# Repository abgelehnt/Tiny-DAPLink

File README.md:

# Tiny-DAPLink

> 小巧的使用CH552实现的DAPLink

详见[Tiny-DAPLink：开源CH552实现的CMSIS-DAP v2升级版](https://whycan.com/t_9365.html)

## 硬件设计

1. 下载按键需要超级小的两脚小龟按键，如果不重复下载调试，可以不焊
2. 整体需要包热缩管进行绝缘，不然手汗会造成数据异常

## DAT命令列表

使用任意串口工具发送特定的命令即可对Tiny-DAPLink进行相应的设置。

| 命令            | 描述                                                 |
|:--------------|:---------------------------------------------------|
| DAT+RST       | 重启调试器                                              |
| DAT+IAP       | 进入调试器固件下载模式                                        |
| DAT+KEY?      | 查询电容键盘映射的按键                                        |
| DAT+KEY=XX    | 更改电容键盘映射的按键[USB CDC键盘键值表](3.Docs/Keyboard_HID.txt) |
| DAT+KEY=FF    | 关闭电容键盘功能                                           |
| DAT+AUTHOR?   | 查询作者信息                                             |
| DAT+KEY_FLASH | 刷新电容按键参数                                           |
| DAT+KEY_VALUE | 查看电容按键参数                                           |

## 注意事项

1. 一些不合格的数据线会使Type C接口外壳对地短路，使电容按键失效

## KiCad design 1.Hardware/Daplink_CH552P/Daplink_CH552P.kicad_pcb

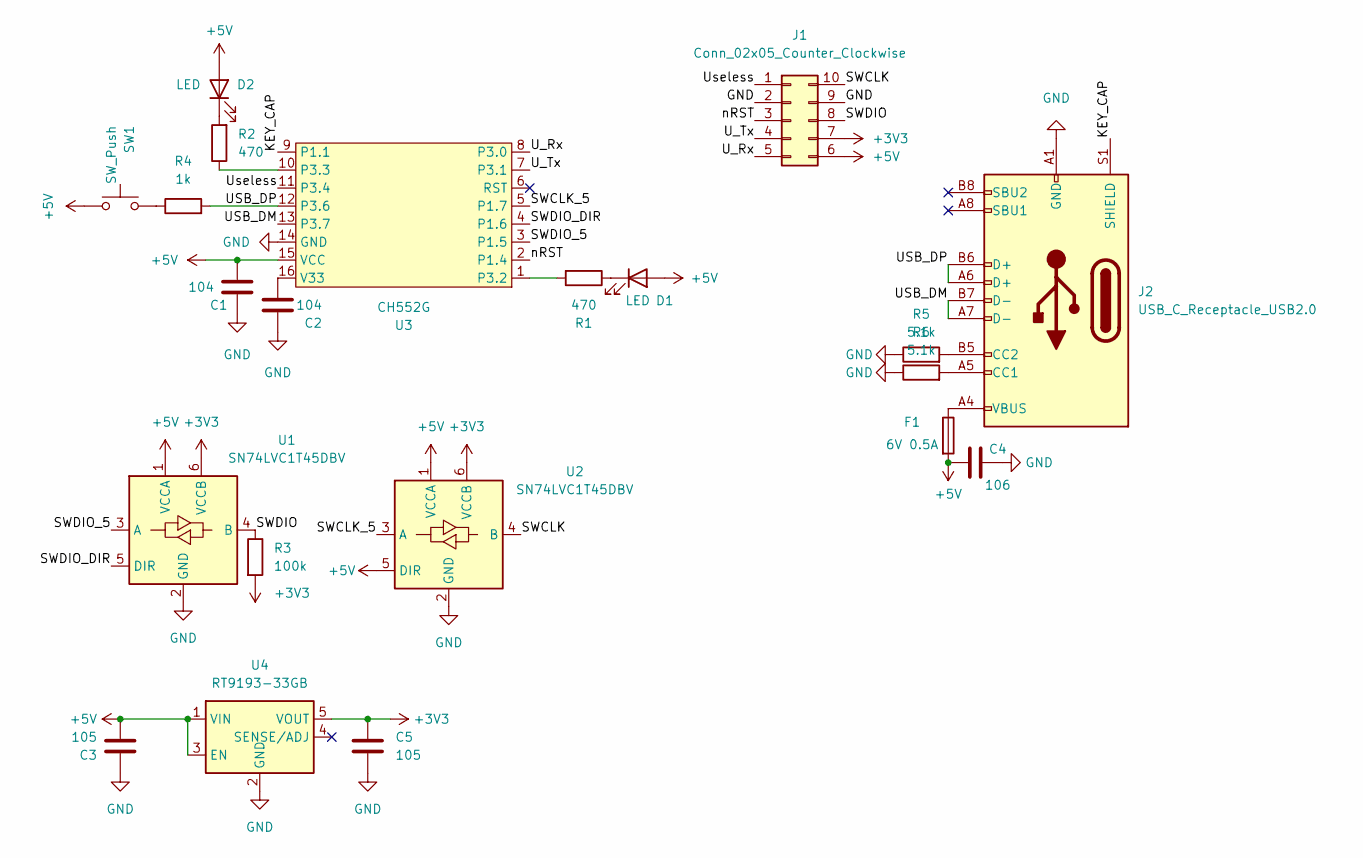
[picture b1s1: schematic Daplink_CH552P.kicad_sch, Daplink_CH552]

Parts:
C1, C2: 104; C_0603_1608Metric
C3, C5: 105; C_0603_1608Metric
C4: 106; C_0805_2012Metric
D1, D2: LED; LED_0603_1608Metric
F1: 6V 0.5A; Fuse_0603_1608Metric
J1: Conn_02x05_Counter_Clockwise; Connector_2.54mm_2_5P_SMD
J2: USB_C_Receptacle_USB2.0; USB_C_Receptacle_HRO_TYPE-C-31-M-12
R1, R2: 470; R_0603_1608Metric
R3: 100k; R_0603_1608Metric
R4: 1k; R_0603_1608Metric
R5, R6: 5.1k; R_0603_1608Metric
SW1: SW_Push; SW_SPST_B3U-1000P
U1, U2: SN74LVC1T45DBV; SOT-23-6
U3: CH552G; SOP-16_3.9x9.9mm_P1.27mm
U4: RT9193-33GB; TSOT-23-5

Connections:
+3V3: C5.2, J1.7, R3.2, U1.6 (VCCB), U2.6 (VCCB), U4.5 (VOUT)
+5V: C1.1, C3.1, C4.1, D1.2 (A), D2.2 (A), F1.2, J1.6, SW1.1, U1.1 (VCCA), U2.1 (VCCA), U2.5 (DIR), U3.15 (VCC), U4.1 (VIN), U4.3 (EN)
/KEY_CAP: J2.S1 (SHIELD), U3.9 (P1.1)
/SWCLK: J1.10, U2.4 (B)
/SWCLK_5: U2.3 (A), U3.5 (P1.7)
/SWDIO: J1.8, R3.1, U1.4 (B)
/SWDIO_5: U1.3 (A), U3.3 (P1.5)
/SWDIO_DIR: U1.5 (DIR), U3.4 (P1.6)
/USB_DM: J2.A7 (D-), J2.B7 (D-), U3.13 (P3.7)
/USB_DP: J2.A6 (D+), J2.B6 (D+), R4.2, U3.12 (P3.6)
/U_Rx: J1.5, U3.8 (P3.0)
/U_Tx: J1.4, U3.7 (P3.1)
/Useless: J1.1, U3.11 (P3.4)
/nRST: J1.3, U3.2 (P1.4)
GND: C1.2, C2.1, C3.2, C4.2, C5.1, J1.2, J1.9, J2.A1 (GND), J2.A12 (GND), J2.B1 (GND), J2.B12 (GND), R5.1, R6.1, U1.2 (GND), U2.2 (GND), U3.14 (GND), U4.2 (GND)
unnamed: C2.2, U3.16 (V33)
unnamed: D1.1 (K), R1.1
unnamed: D2.1 (K), R2.2
unnamed: F1.1, J2.A4 (VBUS), J2.A9 (VBUS), J2.B4 (VBUS), J2.B9 (VBUS)
unnamed: J2.A5 (CC1), R6.2
unnamed: J2.B5 (CC2), R5.2
unnamed: R1.2, U3.1 (P3.2)
unnamed: R2.1, U3.10 (P3.3)
unnamed: R4.1, SW1.2

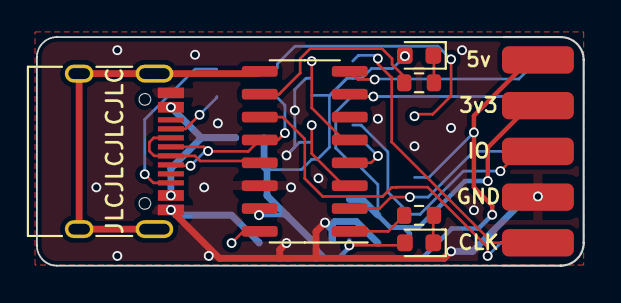
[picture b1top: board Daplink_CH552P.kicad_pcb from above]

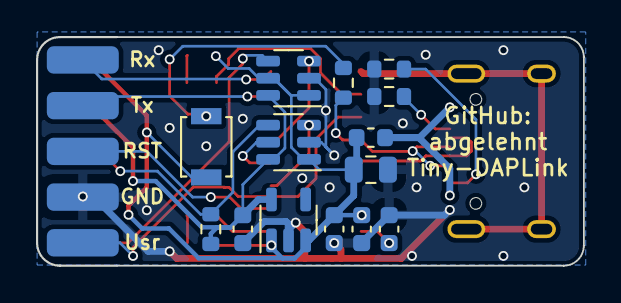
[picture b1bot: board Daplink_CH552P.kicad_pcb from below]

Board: 2 copper layers, 30.4 x 12.7 mm, 21 parts (15 on the bottom side), 24 nets.

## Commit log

2023-01-08 Init
2023-01-10 无关紧要的修改
2023-01-11 串口部分初步可用
2023-01-11 新增AT文件
2023-01-11 串口部分完全写完
2023-01-11 解决可变序列号 串口发现问题：第一次发送的数据错误
2023-01-11 解决串口问题
2023-01-12 找到下载功能无法使用原因：RAM爆了
2023-01-12 找到下载不能用的原因：汇编代码问题，但是串口烂了
2023-01-12 串口问题解决 下载器可以完美使用
2023-01-12 开启睡眠功能
2023-01-13 touch key基本可用
2023-01-13 修正配置描述符
2023-01-13 电容按键做键盘完美运行
2023-01-14 更正IO配置问题：使用推挽输出，准双向口输入
2023-01-21 PSW.PF优化校验速度 使用SPI刷写 数据搬运过程使用汇编优化
2023-01-21 更改项目结构
2023-01-23 增加AT+AUTHOR AT+KEY?
2023-01-27 更新帖子地址
2023-02-01 更新调试器硬件（未测试）
2023-02-01 更新硬件（未测试）
2023-02-05 清楚不必要文件
2023-02-05 补全3D模型
2023-02-07 添加DTR引脚 开始画第二个板子
2023-02-26 使用中断嵌套
2023-04-18 完成电容按键部分
2023-04-18 电容按键阈值可变
2023-04-18 更新README
2023-04-22 优化项目代码 解决了按键更改偶尔不生效的问题
